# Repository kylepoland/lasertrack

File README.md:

# LaserTrack

A 3D-printed TV set-top box that takes NFC cartridges. Personal project.

- `cad/` — parametric models in Python (build123d)
- `firmware/` — microcontroller code
- `software/` — Raspberry Pi software (daemon, FieldStation42 setup)
- `electronics/` — wiring and pin maps
- `docs/` — decisions and notes
- `vendor/` — third-party part models and datasheets

## Building a model

```bash
cd cad
uv sync
uv run python models/tolerance_gauge.py
```

STEP files land in `cad/out/`. Open them in FreeCAD to inspect, or in Bambu
Studio to slice.

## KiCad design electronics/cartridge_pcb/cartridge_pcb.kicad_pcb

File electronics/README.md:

# Electronics

Wiring is documented as pin-map tables, one file per subsystem. Nothing is
designed yet; the table below is the format to follow.

## Pin-map template

Board: _name_ — logic level: _3.3 V / 5 V_ — powered from: _source_

| Signal | Board pin | Connects to | Device pin | Notes |
|---|---|---|---|---|
| _example: I2C SDA_ | _GPIO 21_ | _NFC reader_ | _SDA_ | _3.3 V only_ |

## Power

| Rail | Source | Loads | Estimated current |
|---|---|---|---|
| 5 V | Mean Well GST25 5 V 4 A supply → panel 5.5 x 2.1 jack → short barrel-to-USB-C lead → Pi USB-C | Pi 4, fan, screen backlight, cartridge LEDs (later) | ~3 A peak (Pi 4 under load ~1.5 A + USB) |
| 3.3 V | Pi's regulator (pins 1, 17) | RC522, screen logic, IR receiver | < 100 mA |

Parts to buy for the box: `box-parts.md`; for the cartridge and slot boards:
`board-parts.md` (generated by `tools/bom.py`).

## Custom boards (KiCad)

| Board | KiCad project | Pin map |
|---|---|---|
| Cartridge PCB (CH32V006, contact pads) | `cartridge_pcb/` | `cartridge_pcb.md` |
| Slot PCB (pogo pins, power switching) | `slot_pcb/` | `slot_pcb.md` |

Both schematics are generated from `tools/boards.py` (a netlist in Python;
`tools/kicad_gen.py` writes the KiCad files). Edit `boards.py`, then:

```bash
python3 electronics/tools/boards.py
/Applications/KiCad/KiCad.app/Contents/MacOS/kicad-cli sch erc electronics/cartridge_pcb/cartridge_pcb.kicad_sch
/Applications/KiCad/KiCad.app/Contents/MacOS/kicad-cli sch erc electronics/slot_pcb/slot_pcb.kicad_sch
```

Project symbols and footprints (the CH32V006F8U6, the gold contact pad, the
Mill-Max 0906 pin) are in `lib/`. Every net label on the schematic is a
connection: two pins with the same label are joined.

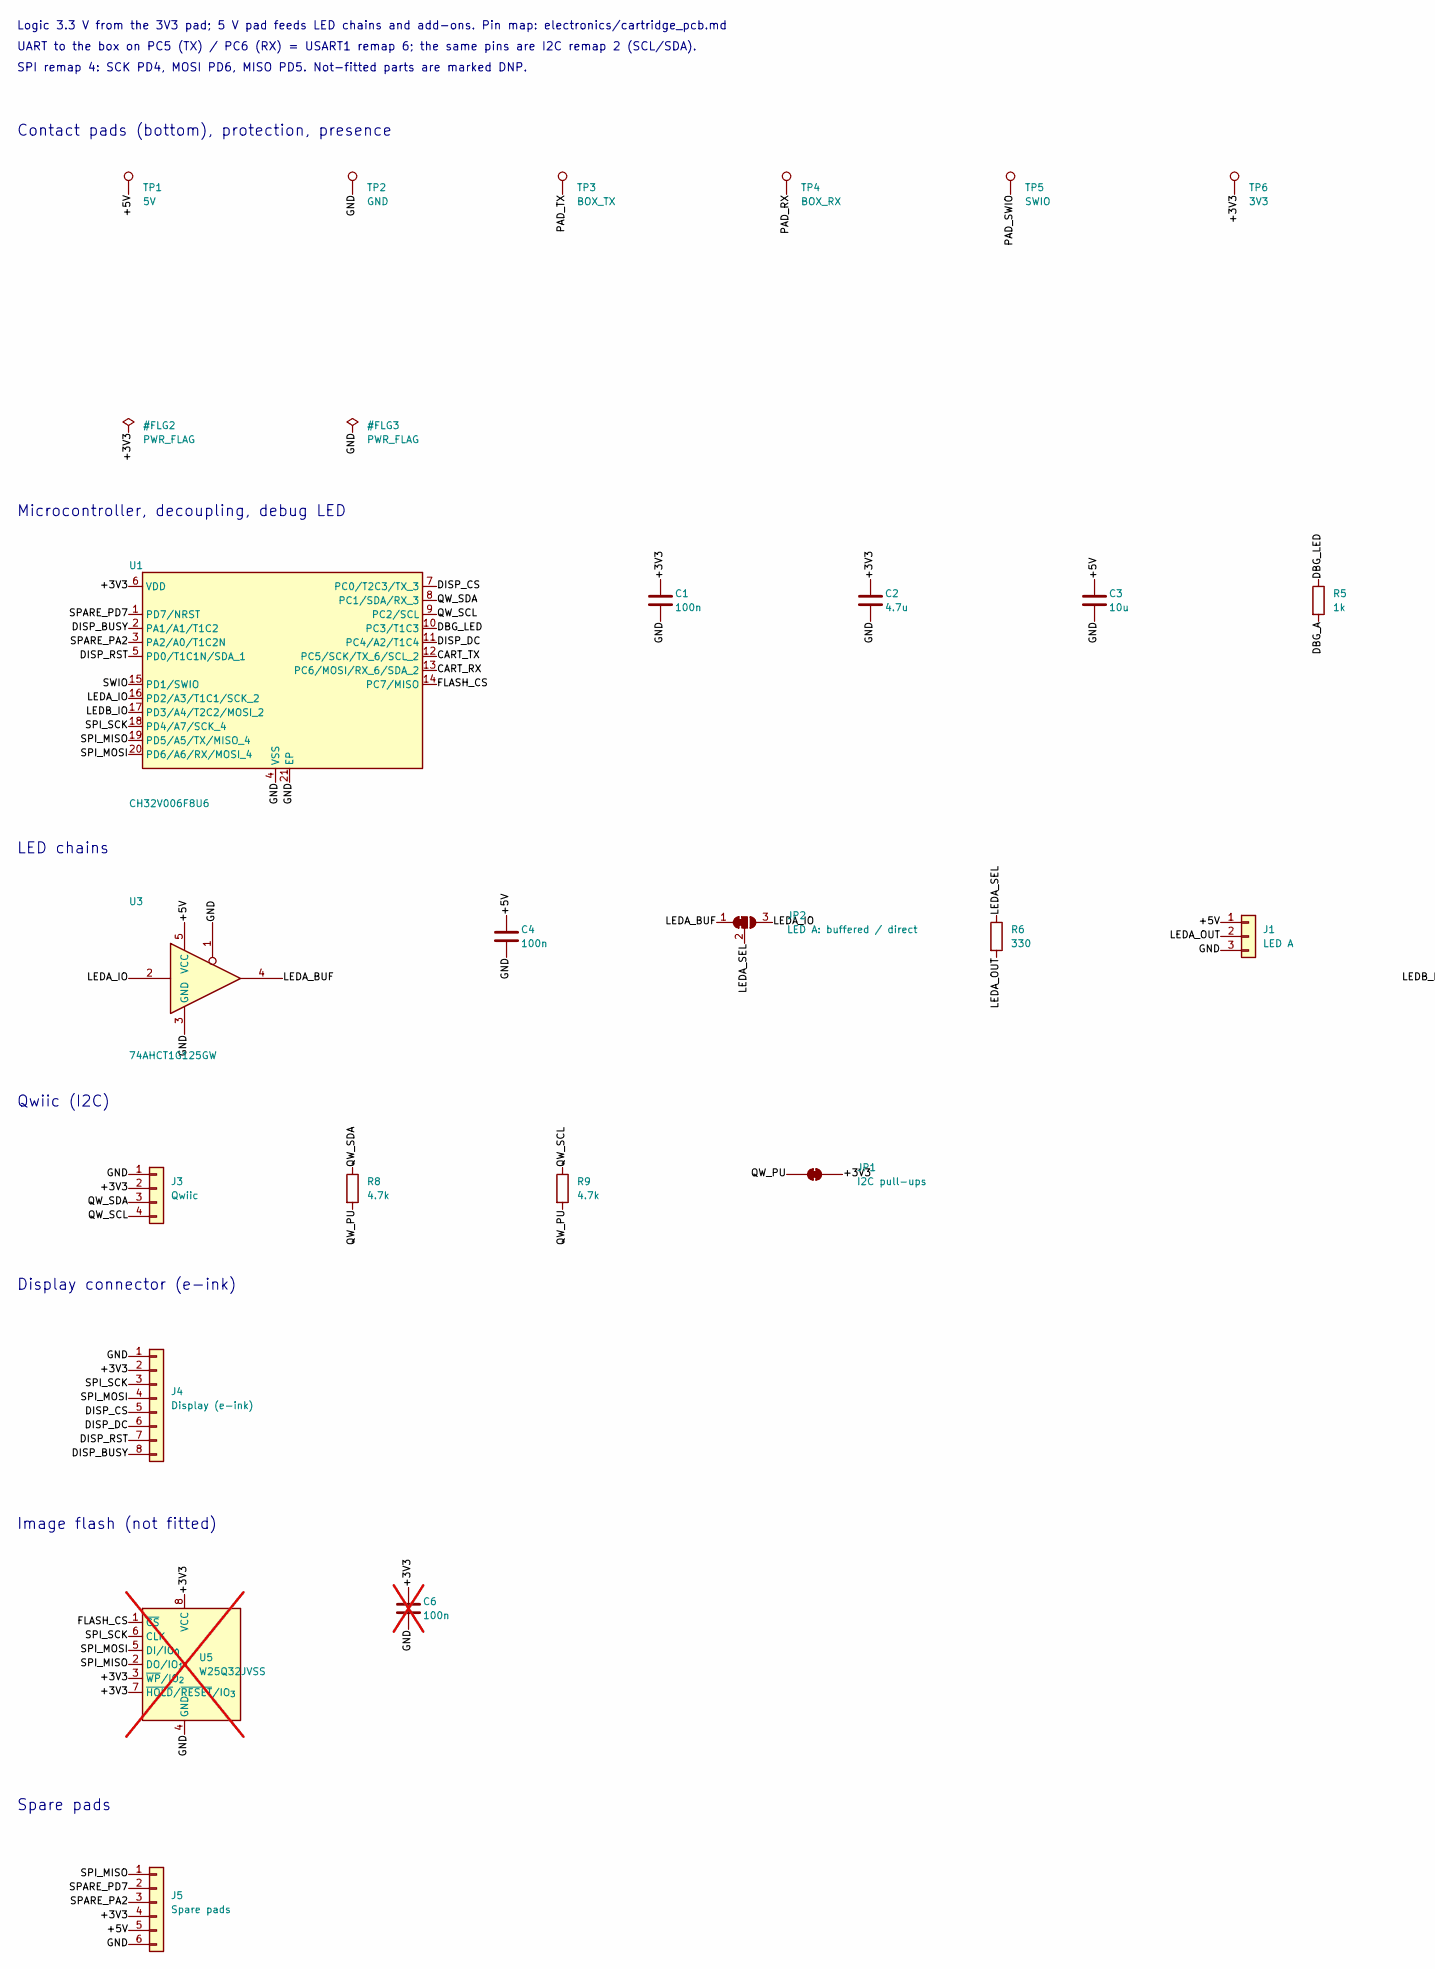
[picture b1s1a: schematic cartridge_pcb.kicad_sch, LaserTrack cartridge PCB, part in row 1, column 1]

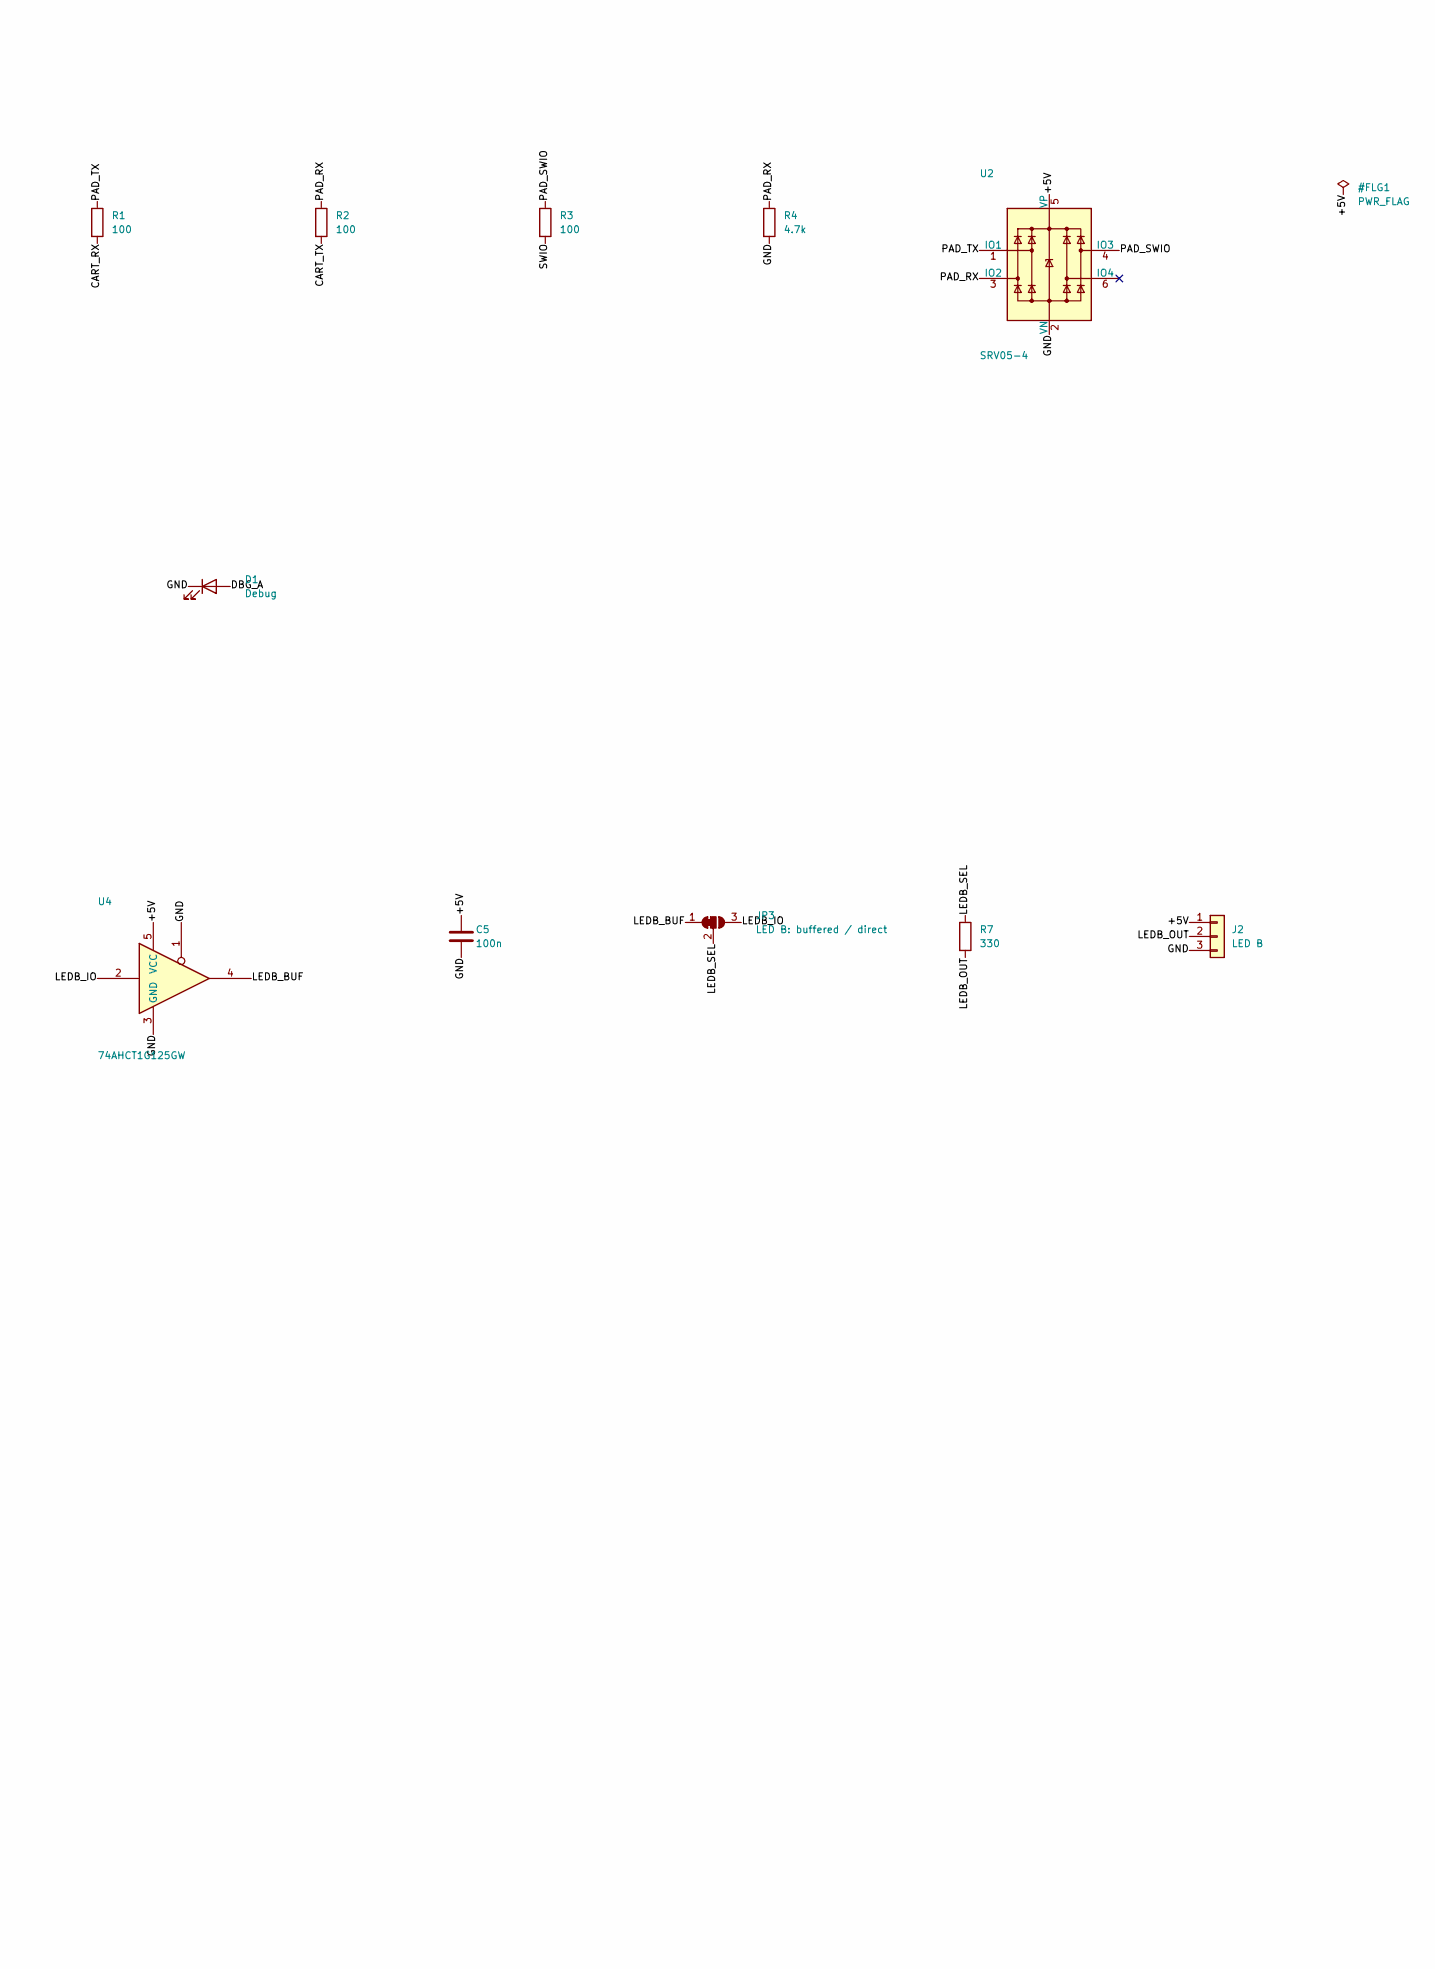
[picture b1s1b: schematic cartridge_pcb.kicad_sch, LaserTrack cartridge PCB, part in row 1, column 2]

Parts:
C1, C4, C5: 100n; C_0402_1005Metric
C2: 4.7u; C_0603_1608Metric
C3: 10u; C_0603_1608Metric
C6: 100n; C_0402_1005Metric; not fitted
D1: Debug; LED_0603_1608Metric
J1: LED A; JST_SH_BM03B-SRSS-TB_1x03-1MP_P1.00mm_Vertical
J2: LED B; JST_SH_BM03B-SRSS-TB_1x03-1MP_P1.00mm_Vertical
J3: Qwiic; JST_SH_BM04B-SRSS-TB_1x04-1MP_P1.00mm_Vertical
J4: Display (e-ink); JST_SH_BM08B-SRSS-TB_1x08-1MP_P1.00mm_Vertical
J5: Spare pads; SparePads_2x3_P1.5mm
JP1: I2C pull-ups; SolderJumper-2_P1.3mm_Bridged_RoundedPad1.0x1.5mm
JP2: LED A: buffered / direct; SolderJumper-3_P1.3mm_Bridged12_RoundedPad1.0x1.5mm
JP3: LED B: buffered / direct; SolderJumper-3_P1.3mm_Bridged12_RoundedPad1.0x1.5mm
R1, R2, R3: 100; R_0402_1005Metric
R4, R8, R9: 4.7k; R_0402_1005Metric
R5: 1k; R_0402_1005Metric
R6, R7: 330; R_0402_1005Metric
TP1: 5V; ContactPad_3x4mm
TP2: GND; ContactPad_3x4mm
TP3: BOX_TX; ContactPad_3x4mm
TP4: BOX_RX; ContactPad_3x4mm
TP5: SWIO; ContactPad_3x4mm
TP6: 3V3; ContactPad_3x4mm
U1: CH32V006F8U6; QFN-20-1EP_3x3mm_P0.4mm_EP1.65x1.65mm; LCSC C42431288
U2: SRV05-4; SOT-23-6
U3, U4: 74AHCT1G125GW; SOT-353_SC-70-5
U5: W25Q32JVSS; SOIC-8_3.9x4.9mm_P1.27mm; not fitted

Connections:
/+3V3: C1.1, C2.1, C6.1, J3.2, J4.2, J5.4, JP1.2 (B), TP6.1, U1.6 (VDD), U5.3 (~WP/IO_{2}), U5.7 (~HOLD/~RESET/IO_{3}), U5.8 (VCC)
/+5V: C3.1, C4.1, C5.1, J1.1, J2.1, J5.5, TP1.1, U2.5 (VP), U3.5 (VCC), U4.5 (VCC)
/CART_RX: R1.2, U1.13 (PC6/MOSI/RX_6/SDA_2)
/CART_TX: R2.2, U1.12 (PC5/SCK/TX_6/SCL_2)
/DBG_A: D1.2 (A), R5.2
/DBG_LED: R5.1, U1.10 (PC3/T1C3)
/DISP_BUSY: J4.8, U1.2 (PA1/A1/T1C2)
/DISP_CS: J4.5, U1.7 (PC0/T2C3/TX_3)
/DISP_DC: J4.6, U1.11 (PC4/A2/T1C4)
/DISP_RST: J4.7, U1.5 (PD0/T1C1N/SDA_1)
/FLASH_CS: U1.14 (PC7/MISO), U5.1 (~CS)
/GND: C1.2, C2.2, C3.2, C4.2, C5.2, C6.2, D1.1 (K), J1.3, J2.3, J3.1, J4.1, J5.6, R4.2, TP2.1, U1.4 (VSS), U1.21 (EP), U2.2 (VN), U3.1, U3.3 (GND), U4.1, U4.3 (GND), U5.4 (GND)
/LEDA_BUF: JP2.1 (A), U3.4
/LEDA_IO: JP2.3 (B), U1.16 (PD2/A3/T1C1/SCK_2), U3.2
/LEDA_OUT: J1.2, R6.2
/LEDA_SEL: JP2.2 (C), R6.1
/LEDB_BUF: JP3.1 (A), U4.4
/LEDB_IO: JP3.3 (B), U1.17 (PD3/A4/T2C2/MOSI_2), U4.2
/LEDB_OUT: J2.2, R7.2
/LEDB_SEL: JP3.2 (C), R7.1
/PAD_RX: R2.1, R4.1, TP4.1, U2.3 (IO2)
/PAD_SWIO: R3.1, TP5.1, U2.4 (IO3)
/PAD_TX: R1.1, TP3.1, U2.1 (IO1)
/QW_PU: JP1.1 (A), R8.2, R9.2
/QW_SCL: J3.4, R9.1, U1.9 (PC2/SCL)
/QW_SDA: J3.3, R8.1, U1.8 (PC1/SDA/RX_3)
/SPARE_PA2: J5.3, U1.3 (PA2/A0/T1C2N)
/SPARE_PD7: J5.2, U1.1 (PD7/NRST)
/SPI_MISO: J5.1, U1.19 (PD5/A5/TX/MISO_4), U5.2 (DO/IO_{1})
/SPI_MOSI: J4.4, U1.20 (PD6/A6/RX/MOSI_4), U5.5 (DI/IO_{0})
/SPI_SCK: J4.3, U1.18 (PD4/A7/SCK_4), U5.6 (CLK)
/SWIO: R3.2, U1.15 (PD1/SWIO)

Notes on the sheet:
Contact pads (bottom), protection, presence
Microcontroller, decoupling, debug LED
LED chains
Qwiic (I2C)
Display connector (e-ink)
Image flash (not fitted)
Spare pads
Logic 3.3 V from the 3V3 pad; 5 V pad feeds LED chains and add-ons. Pin map: electronics/cartridge_pcb.md
UART to the box on PC5 (TX) / PC6 (RX) = USART1 remap 6; the same pins are I2C remap 2 (SCL/SDA).
SPI remap 4: SCK PD4, MOSI PD6, MISO PD5. Not-fitted parts are marked DNP.

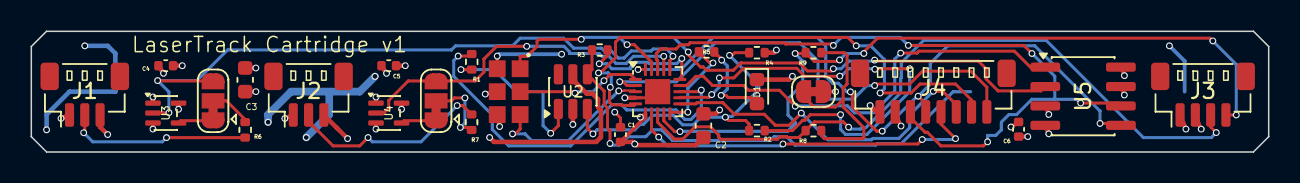
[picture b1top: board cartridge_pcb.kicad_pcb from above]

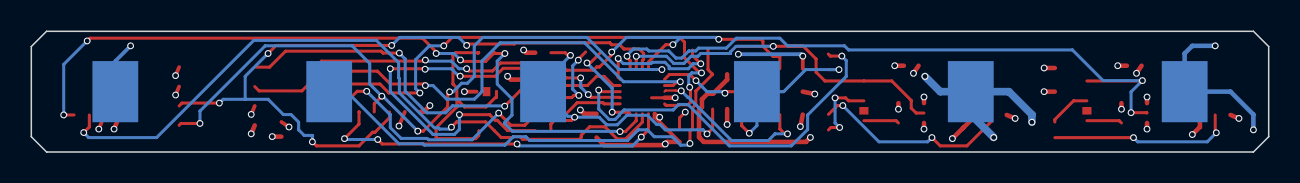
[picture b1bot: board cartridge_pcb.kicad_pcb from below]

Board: 4 copper layers, 81.0 x 7.9 mm, 35 parts (6 on the bottom side), 32 nets.

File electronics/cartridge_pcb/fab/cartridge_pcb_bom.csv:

Comment,Designator,Footprint,LCSC Part #
100n,"C1,C4,C5",0402,C1525
4.7u,C2,0603,C19666
10u,C3,0603,C19702
LED,D1,0603,C2286
BM03B-SRSS-TB,"J1,J2",JST_SH_BM03B-SRSS-TB_1x03-1MP_P1.00mm_Vertical,
BM04B-SRSS-TB,J3,JST_SH_BM04B-SRSS-TB_1x04-1MP_P1.00mm_Vertical,
BM08B-SRSS-TB,J4,JST_SH_BM08B-SRSS-TB_1x08-1MP_P1.00mm_Vertical,
100,"R1,R2,R3",0402,C25076
4.7k,"R4,R8,R9",0402,C25900
1k,R5,0402,C11702
330,"R6,R7",0402,C25104
CH32V006F8U6,U1,QFN-20-1EP_3x3mm_P0.4mm_EP1.65x1.65mm,C42431288
SRV05-4,U2,SOT-23-6,
74AHCT1G125GW,"U3,U4",SOT-353_SC-70-5,

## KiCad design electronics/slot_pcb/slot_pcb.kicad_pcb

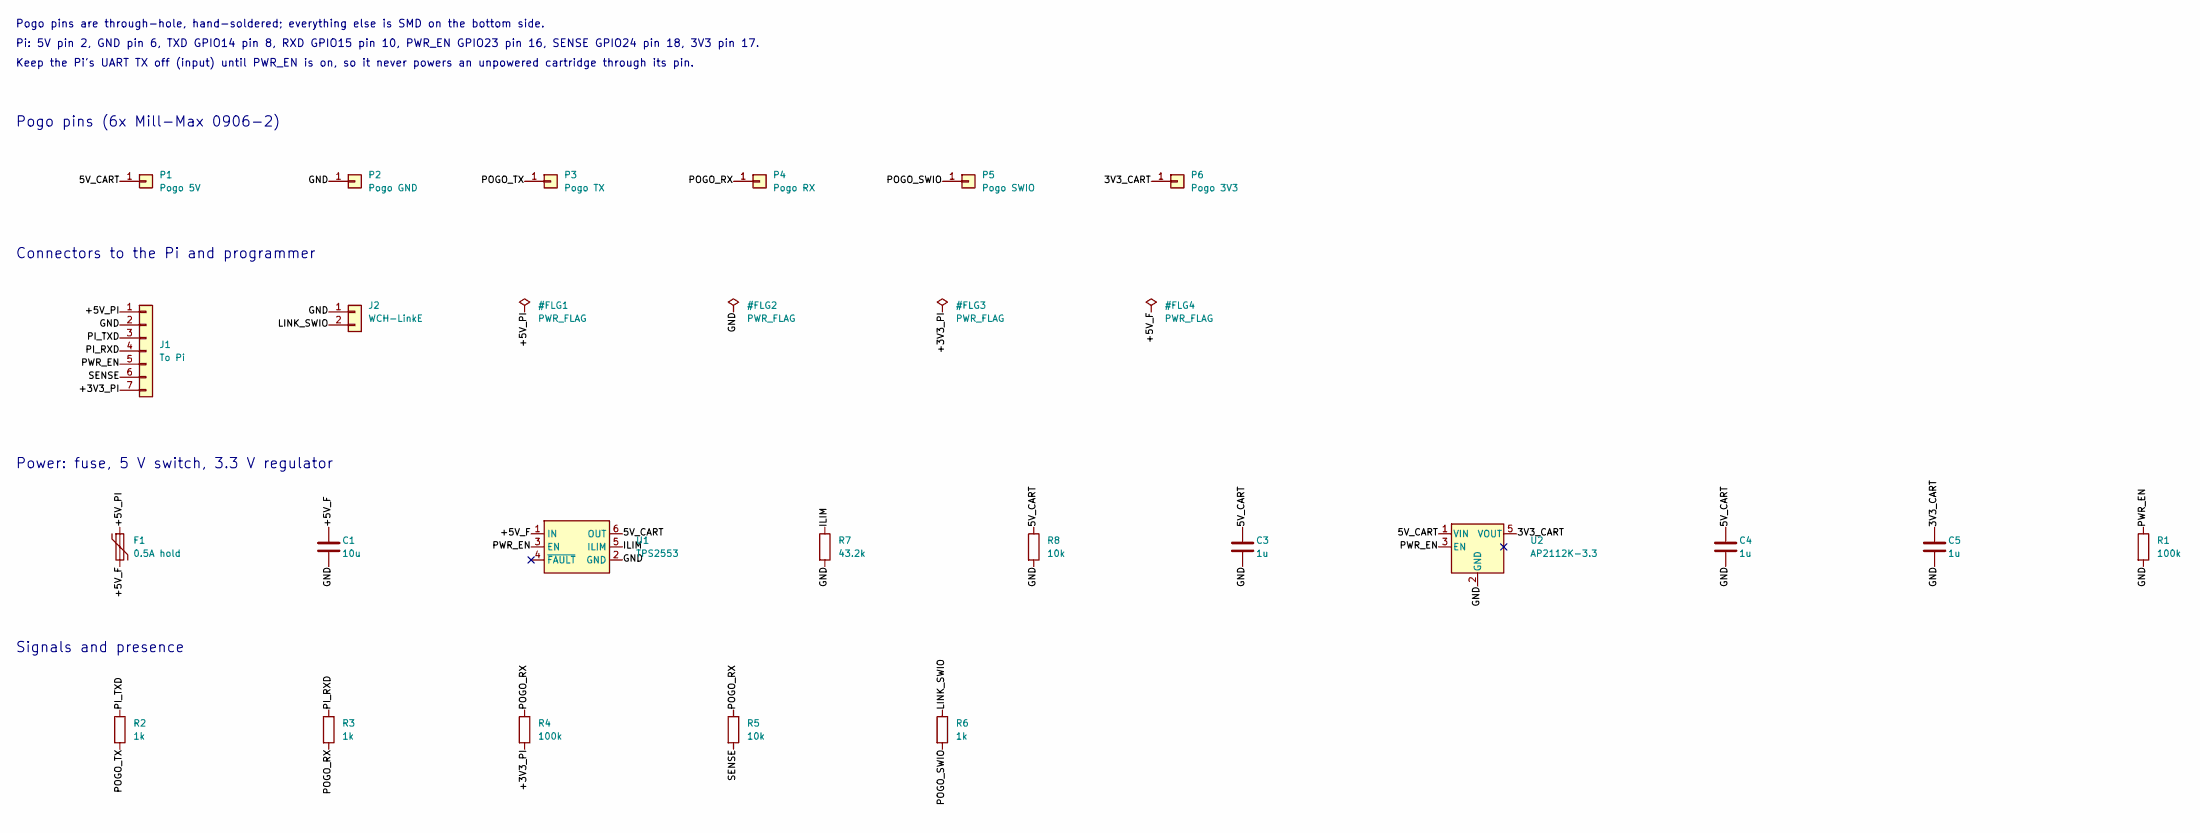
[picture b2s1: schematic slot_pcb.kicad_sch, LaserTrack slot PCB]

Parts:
C1: 10u; C_0603_1608Metric
C3, C4, C5: 1u; C_0402_1005Metric
F1: 0.5A hold; Fuse_1206_3216Metric
J1: To Pi; PinHeader_1x07_P2.54mm_Vertical
J2: WCH-LinkE; PinHeader_1x02_P2.54mm_Vertical
P1: Pogo 5V; MillMax_0906_TH
P2: Pogo GND; MillMax_0906_TH
P3: Pogo TX; MillMax_0906_TH
P4: Pogo RX; MillMax_0906_TH
P5: Pogo SWIO; MillMax_0906_TH
P6: Pogo 3V3; MillMax_0906_TH
R1, R4: 100k; R_0402_1005Metric
R2, R3, R6: 1k; R_0402_1005Metric
R5, R8: 10k; R_0402_1005Metric
R7: 43.2k; R_0402_1005Metric
U1: TPS2553; SOT-23-6
U2: AP2112K-3.3; SOT-23-5

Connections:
/3V3_CART: C5.1, P6.1, U2.5 (VOUT)
/5V_CART: C3.1, C4.1, P1.1, R8.1, U1.6 (OUT), U2.1 (VIN)
/+3V3_PI: J1.7, R4.2
/+5V_F: C1.1, F1.2, U1.1 (IN)
/+5V_PI: F1.1, J1.1
/GND: C1.2, C3.2, C4.2, C5.2, J1.2, J2.1, P2.1, R1.2, R7.2, R8.2, U1.2 (GND), U2.2 (GND)
/ILIM: R7.1, U1.5 (ILIM)
/LINK_SWIO: J2.2, R6.1
/PI_RXD: J1.4, R3.1
/PI_TXD: J1.3, R2.1
/POGO_RX: P4.1, R3.2, R4.1, R5.1
/POGO_SWIO: P5.1, R6.2
/POGO_TX: P3.1, R2.2
/PWR_EN: J1.5, R1.1, U1.3 (EN), U2.3 (EN)
/SENSE: J1.6, R5.2

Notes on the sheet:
Pogo pins (6x Mill-Max 0906-2)
Connectors to the Pi and programmer
Power: fuse, 5 V switch, 3.3 V regulator
Signals and presence
Pogo pins are through-hole, hand-soldered; everything else is SMD on the bottom side.
Pi: 5V pin 2, GND pin 6, TXD GPIO14 pin 8, RXD GPIO15 pin 10, PWR_EN GPIO23 pin 16, SENSE GPIO24 pin 18, 3V3 pin 17.
Keep the Pi's UART TX off (input) until PWR_EN is on, so it never powers an unpowered cartridge through its pin.

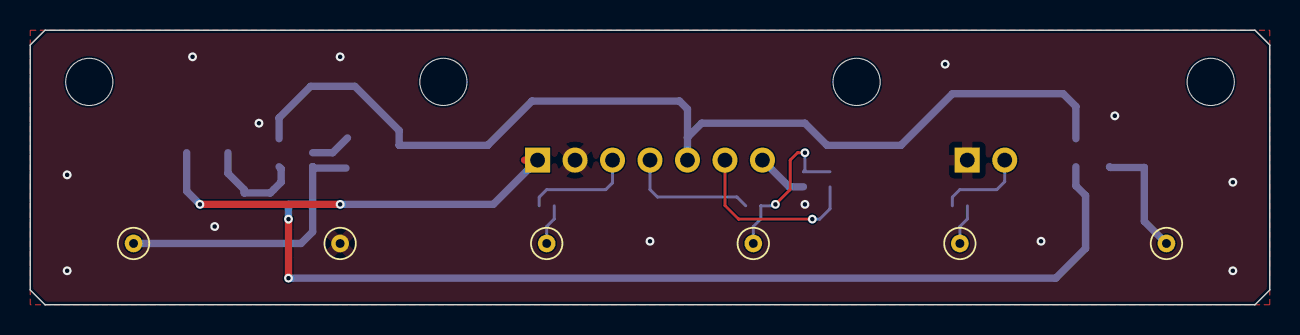
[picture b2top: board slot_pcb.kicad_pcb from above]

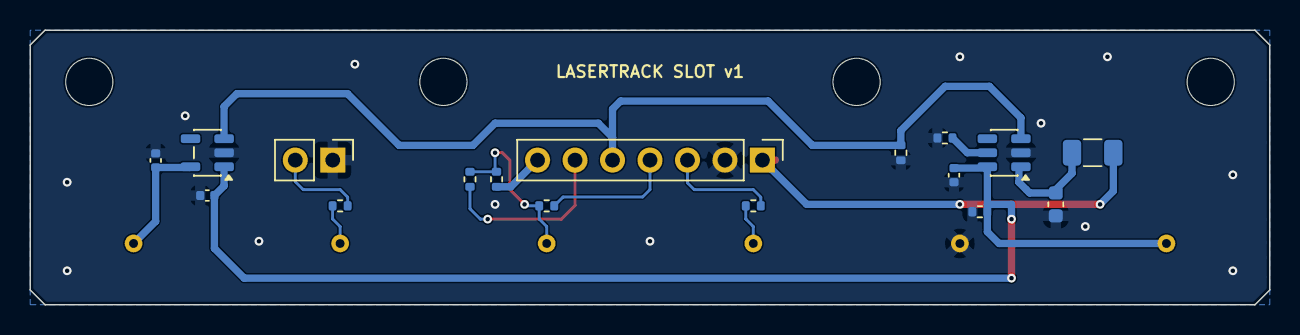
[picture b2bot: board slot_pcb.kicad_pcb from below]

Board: 2 copper layers, 84.0 x 18.6 mm, 27 parts (17 on the bottom side), 15 nets.

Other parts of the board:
H1, H2, H3, H4: MountingHole_3.2mm_M3

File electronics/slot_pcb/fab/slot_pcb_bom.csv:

Comment,Designator,Footprint,LCSC Part #
10u,C1,0603,C19702
1u,"C3,C4,C5",0402,
0.5A hold,F1,Fuse_1206_3216Metric,
To Pi,J1,PinHeader_1x07_P2.54mm_Vertical,
WCH-LinkE,J2,PinHeader_1x02_P2.54mm_Vertical,
Pogo 5V,P1,MillMax_0906_TH,
Pogo GND,P2,MillMax_0906_TH,
Pogo TX,P3,MillMax_0906_TH,
Pogo RX,P4,MillMax_0906_TH,
Pogo SWIO,P5,MillMax_0906_TH,
Pogo 3V3,P6,MillMax_0906_TH,
100k,"R1,R4",0402,C25741
1k,"R2,R3,R6",0402,C11702
10k,"R5,R8",0402,
43.2k,R7,0402,
TPS2553,U1,SOT-23-6,
AP2112K-3.3,U2,SOT-23-5,

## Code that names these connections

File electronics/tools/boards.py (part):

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
def mcu_symbol():
    io, pw = "bidirectional", "power_in"
    left = [("6", "VDD", pw), None, ("1", "PD7/NRST", io), ("2", "PA1/A1/T1C2", io),
            ("3", "PA2/A0/T1C2N", io), ("5", "PD0/T1C1N/SDA_1", io), None, ("15", "PD1/SWIO", io),
            ("16", "PD2/A3/T1C1/SCK_2", io), ("17", "PD3/A4/T2C2/MOSI_2", io),
            ("18", "PD4/A7/SCK_4", io), ("19", "PD5/A5/TX/MISO_4", io), ("20", "PD6/A6/RX/MOSI_4", io)]
    right = [("7", "PC0/T2C3/TX_3", io), ("8", "PC1/SDA/RX_3", io), ("9", "PC2/SCL", io),
             ("10", "PC3/T1C3", io), ("11", "PC4/A2/T1C4", io), ("12", "PC5/SCK/TX_6/SCL_2", io),
             ("13", "PC6/MOSI/RX_6/SDA_2", io), ("14", "PC7/MISO", io)]
    bottom = [("4", "VSS", pw), ("21", "EP", pw)]
    return ic_symbol(
        "CH32V006F8U6", "U", MCU_FP, left, right, bottom=bottom, width=50.8,
        descr="WCH CH32V006F8U6 RISC-V MCU, 62K flash, 8K RAM, QFN-20 3x3 mm, 0.4 mm pitch. "
              "Exposed pad is VSS. PD7 is also the reset pin and is bonded to PA4 inside the chip.",
        datasheet="https://www.wch-ic.com/products/CH32V006.html")


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                ("5V", "+5V"), ("GND", "GND"), ("BOX_TX", "PAD_TX"), ("BOX_RX", "PAD_RX"),
                ("SWIO", "PAD_SWIO"), ("3V3", "+3V3")])]
    contacts = pads + [
        R("R1", "100", "PAD_TX", "CART_RX", note="Box TX -> cartridge RX (PC6)"),
        R("R2", "100", "PAD_RX", "CART_TX", note="Cartridge TX (PC5) -> box RX"),
        R("R3", "100", "PAD_SWIO", "SWIO"),
        R("R4", "4.7k", "PAD_RX", "GND",
          note="Presence: pulls the box RX line low with power off. Strong enough to beat the Pi's "
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    headers = [
        conn("J1", "To Pi", ["+5V_PI", "GND", "PI_TXD", "PI_RXD", "PWR_EN", "SENSE", "+3V3_PI"],
             "Connector_PinHeader_2.54mm:PinHeader_1x07_P2.54mm_Vertical"),
        conn("J2", "WCH-LinkE", ["GND", "LINK_SWIO"], "Connector_PinHeader_2.54mm:PinHeader_1x02_P2.54mm_Vertical"),
        flag("#FLG1", "+5V_PI"), flag("#FLG2", "GND"), flag("#FLG3", "+3V3_PI"), flag("#FLG4", "+5V_F"),
    ]
    power = [
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    for name, title, groups, notes in (
        ("cartridge_pcb", "LaserTrack cartridge PCB", cartridge_groups(), (
            "Logic 3.3 V from the 3V3 pad; 5 V pad feeds LED chains and add-ons. Pin map: electronics/cartridge_pcb.md",
            "UART to the box on PC5 (TX) / PC6 (RX) = USART1 remap 6; the same pins are I2C remap 2 (SCL/SDA).",
            "SPI remap 4: SCK PD4, MOSI PD6, MISO PD5. Not-fitted parts are marked DNP.")),
        ("slot_pcb", "LaserTrack slot PCB", slot_groups(), (
            "Pogo pins are through-hole, hand-soldered; everything else is SMD on the bottom side.",
            "Pi: 5V pin 2, GND pin 6, TXD GPIO14 pin 8, RXD GPIO15 pin 10, PWR_EN GPIO23 pin 16, SENSE GPIO24 pin 18, 3V3 pin 17.",
            "Keep the Pi's UART TX off (input) until PWR_EN is on, so it never powers an unpowered cartridge through its pin.")),
    ):
        out = ROOT / name
        out.mkdir(exist_ok=True)
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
